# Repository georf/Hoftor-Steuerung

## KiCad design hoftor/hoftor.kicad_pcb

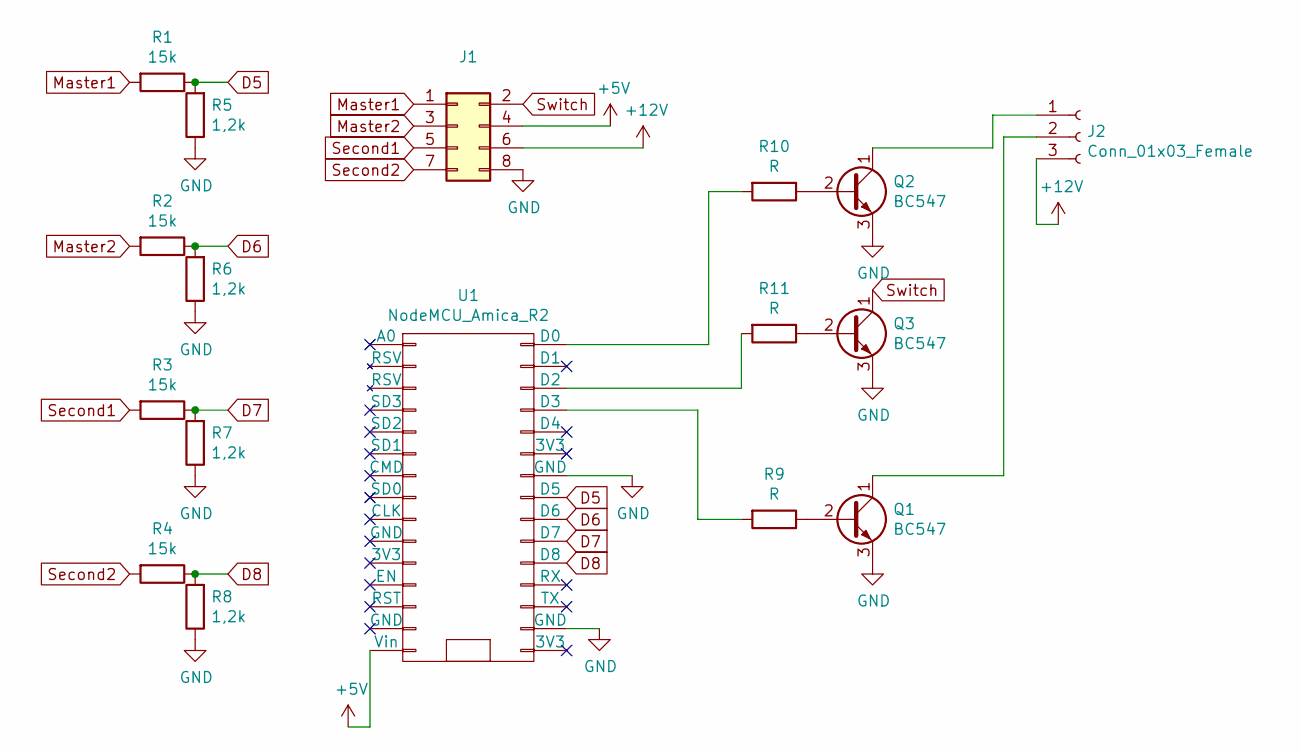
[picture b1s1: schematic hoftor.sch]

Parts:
J1: Conn_02x04_Odd_Even; PinHeader_2x04_P2.54mm_Vertical
J2: Conn_01x03_Female; Connector 3xPin
Q1, Q2, Q3: BC547; TO-92_Inline_Wide
R1, R2, R3, R4: 15k; R_Axial_DIN0207_L6.3mm_D2.5mm_P10.16mm_Horizontal
R5, R8: 1,2k; R_Axial_DIN0207_L6.3mm_D2.5mm_P7.62mm_Horizontal
R6, R7: 1,2k; R_Axial_DIN0207_L6.3mm_D2.5mm_P10.16mm_Horizontal
R9, R10, R11: R; R_Axial_DIN0207_L6.3mm_D2.5mm_P10.16mm_Horizontal
U1: NodeMCU_Amica_R2; node_MCU_ESP8266_longpad

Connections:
+5V: J1.4, U1.15 (Vin)
+12V: J1.6, J2.3
D5: R1.1, R5.2, U1.23 (D5)
D6: R2.1, R6.2, U1.22 (D6)
D7: R3.1, R7.2, U1.21 (D7)
D8: R4.1, R8.2, U1.20 (D8)
GND: J1.8, Q1.3 (E), Q2.3 (E), Q3.3 (E), R5.1, R6.1, R7.1, R8.1, U1.17 (GND), U1.24 (GND)
Master1: J1.1, R1.2
Master2: J1.3, R2.2
unnamed: J2.1, Q2.1 (C)
unnamed: J2.2, Q1.1 (C)
unnamed: Q1.2 (B), R9.1
unnamed: Q2.2 (B), R10.1
unnamed: Q3.2 (B), R11.1
unnamed: R9.2, U1.27 (D3)
unnamed: R10.2, U1.30 (D0)
unnamed: R11.2, U1.28 (D2)
Second1: J1.5, R3.2
Second2: J1.7, R4.2
Switch: J1.2, Q3.1 (C)

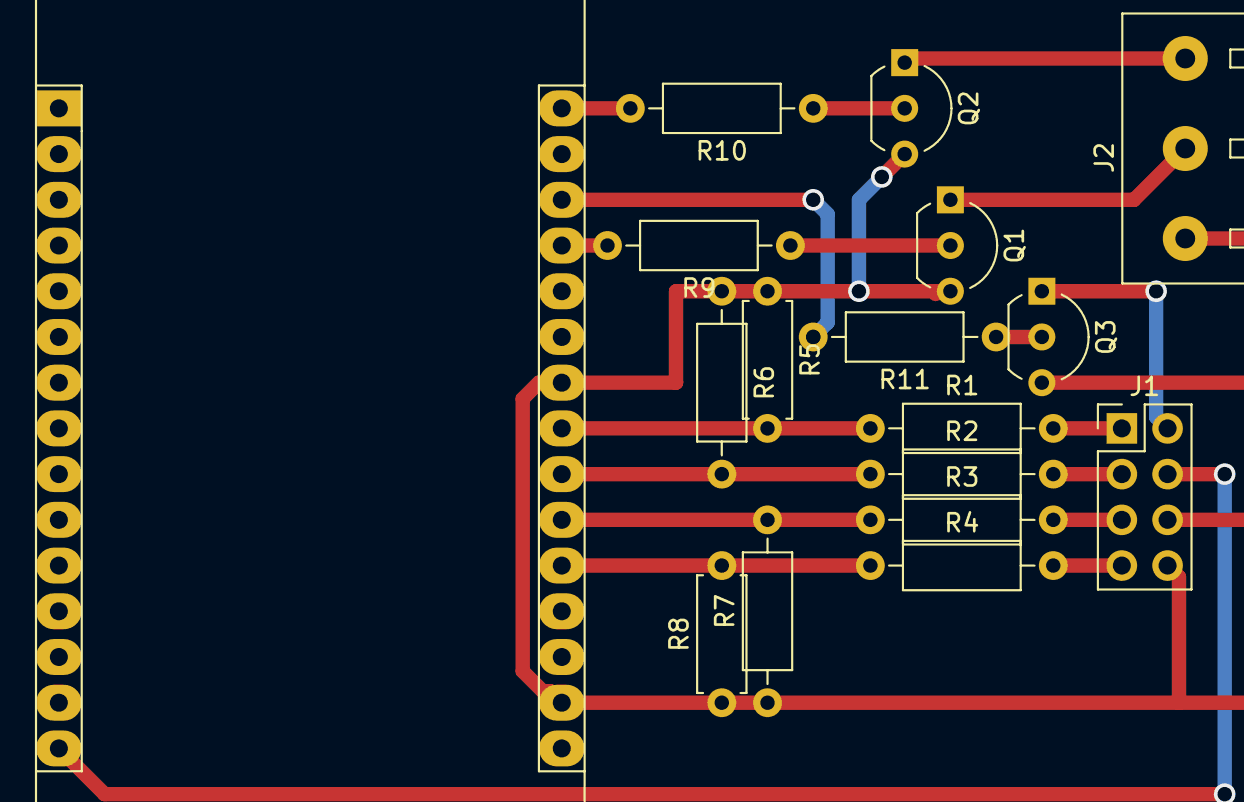
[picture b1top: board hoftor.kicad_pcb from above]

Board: 2 copper layers, 17 parts (0 on the bottom side), 20 nets.

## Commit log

2021-11-01 Software für esp8266 (Wifi, mqtt)
2021-11-01 KiCad-Dateien
